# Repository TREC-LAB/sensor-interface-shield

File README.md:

# PCB Sensor Shield V1.4

## V1.4

V1.4 is the lastest sensor shield and as of 11/8/2022 the current shield on PANDORA

## V2.0 and above

These are actually older than 1.4 and were an old labelling system

## See Connor & Nick, I am learning this readme.md stuff :D

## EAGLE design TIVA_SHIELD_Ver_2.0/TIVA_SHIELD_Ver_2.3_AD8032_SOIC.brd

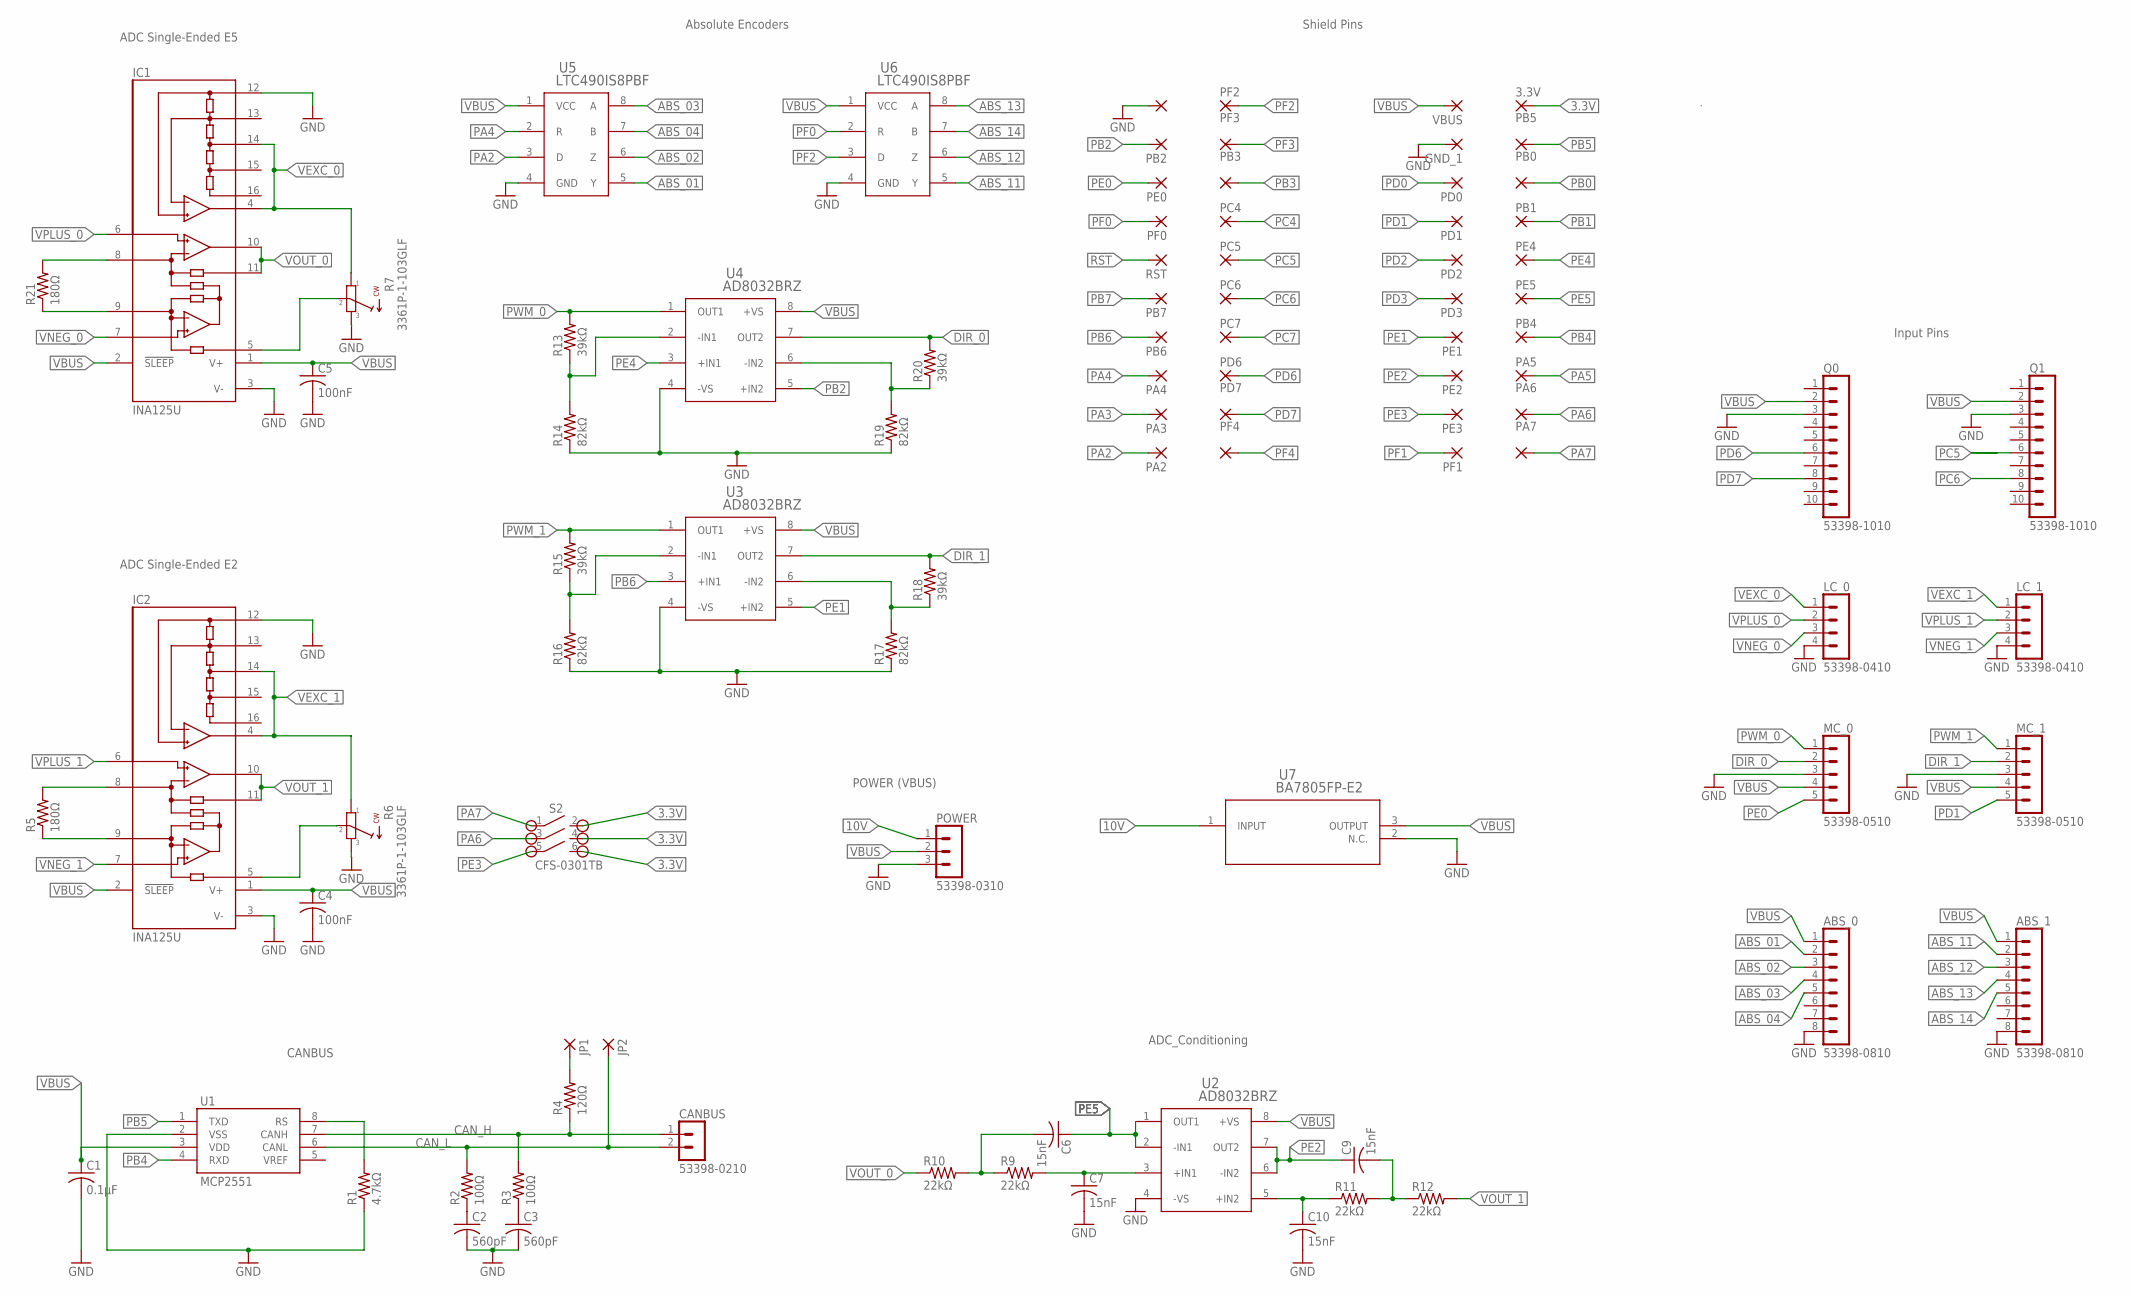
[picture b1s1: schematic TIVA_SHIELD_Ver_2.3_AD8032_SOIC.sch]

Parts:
3.3V: 1,6/0,9
ABS_0, ABS_1: 53398-0810
C1: 0.1µF; C0805
C2, C3: 560pF; C0805
C4, C5: 100nF; C0805
C6, C7, C9, C10: 15nF; C0805
CANBUS: 53398-0210
GND_0, GND_1: 1,6/0,9
IC1, IC2: INA125U; SO16-1
JP1, JP2: 1,6/0,9
LC_0, LC_1: 53398-0410
MC_0, MC_1: 53398-0510
PA2, PA3, PA4, PA5, PA6, PA7: 1,6/0,9
PB0, PB1, PB2, PB3, PB4, PB5, PB6, PB7: 1,6/0,9
PC4, PC5, PC6, PC7: 1,6/0,9
PD0, PD1, PD2, PD3, PD6, PD7: 1,6/0,9
PE0, PE1, PE2, PE3, PE4, PE5: 1,6/0,9
PF0, PF1, PF2, PF3, PF4: 1,6/0,9
POWER: 53398-0310
Q0, Q1: 53398-1010
R1: 4.7kΩ; R0805
R2, R3: 100Ω; R0805
R4: 120Ω; R0805
R5, R21: 180Ω; R0805
R6, R7: 3361P-1-103GLF
R9, R10, R11, R12: 22kΩ; R0805
R13, R15, R18, R20: 39kΩ; R0805
R14, R16, R17, R19: 82kΩ; R0805
RST: 1,6/0,9
S2: CFS-0301TB
U1: MCP2551; SO08
U2, U3, U4: AD8032BRZ; R_8_ADI
U5, U6: LTC490IS8PBF; SO-8_S
U7: BA7805FP-E2; TO252-3_ROM
VBUS: 1,6/0,9

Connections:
3.3V: 3.3V.1, S2.2, S2.4, S2.6
10V: POWER.1, U7.1 (INPUT)
ABS_01: ABS_0.2, U5.5 (Y)
ABS_02: ABS_0.3, U5.6 (Z)
ABS_03: ABS_0.4, U5.8 (A)
ABS_04: ABS_0.5, U5.7 (B)
ABS_11: ABS_1.2, U6.5 (Y)
ABS_12: ABS_1.3, U6.6 (Z)
ABS_13: ABS_1.4, U6.8 (A)
ABS_14: ABS_1.5, U6.7 (B)
CAN_H: CANBUS.1, R3.2, R4.1, U1.7 (CANH)
CAN_L: CANBUS.2, JP2.1, R2.2, U1.6 (CANL)
DIR_0: MC_0.2, R20.2, U4.7 (OUT2)
DIR_1: MC_1.2, R18.2, U3.7 (OUT2)
GND: ABS_0.8, ABS_1.8, C1.2, C2.2, C3.2, C4.2, C5.2, C7.2, C10.2, GND_0.1, GND_1.1, IC1.3 (V-), IC1.12 (REFCOM), IC2.3 (V-), IC2.12 (REFCOM), LC_0.4, LC_1.4, MC_0.3, MC_1.3, POWER.3, Q0.3, Q1.3, R1.1, R6.3, R7.3, R14.1, R16.1, R17.1, R19.1, U1.2 (VSS), U2.4 (-VS), U3.4 (-VS), U4.4 (-VS), U5.4 (GND), U6.4 (GND), U7.2 (N.C.)
unnamed: R1.2, U1.8 (RS)
unnamed: C2.1, R2.1
unnamed: C3.1, R3.1
unnamed: JP1.1, R4.2
unnamed: IC2.9 (RG), R5.1
unnamed: IC2.8 (RG), R5.2
unnamed: IC2.5 (REF), R6.2
unnamed: IC1.9 (RG), R21.1
unnamed: IC1.8 (RG), R21.2
unnamed: IC1.5 (REF), R7.2
unnamed: C10.1, R11.1, U2.5 (+IN2)
unnamed: C9.2, R11.2, R12.1
unnamed: C7.1, R9.2, U2.3 (+IN1)
unnamed: R19.2, R20.1, U4.6 (-IN2)
unnamed: R17.2, R18.1, U3.6 (-IN2)
unnamed: C6.2, R9.1, R10.2
unnamed: R13.1, R14.2, U4.2 (-IN1)
unnamed: R15.1, R16.2, U3.2 (-IN1)
PA2: PA2.1, U5.3 (D)
PA3: PA3.1
PA4: PA4.1, U5.2 (R)
PA5: PA5.1
PA6: PA6.1, S2.3
PA7: PA7.1, S2.1
PB0: PB0.1
PB1: PB1.1
PB2: PB2.1, U4.5 (+IN2)
PB3: PB3.1
PB4: PB4.1, U1.4 (RXD)
PB5: PB5.1, U1.1 (TXD)
PB6: PB6.1, U3.3 (+IN1)
PB7: PB7.1
PC4: PC4.1
PC5: PC5.1, Q1.6
PC6: PC6.1, Q1.8
PC7: PC7.1
PD0: PD0.1
PD1: MC_1.5, PD1.1
PD2: PD2.1
PD3: PD3.1
PD6: PD6.1, Q0.6
PD7: PD7.1, Q0.8
PE0: MC_0.5, PE0.1
PE1: PE1.1, U3.5 (+IN2)
PE2: C9.1, PE2.1, U2.6 (-IN2), U2.7 (OUT2)
PE3: PE3.1, S2.5
PE4: PE4.1, U4.3 (+IN1)
PE5: C6.1, PE5.1, U2.1 (OUT1), U2.2 (-IN1)
PF0: PF0.1, U6.2 (R)
PF1: PF1.1
PF2: PF2.1, U6.3 (D)
PF3: PF3.1
PF4: PF4.1
PWM_0: MC_0.1, R13.2, U4.1 (OUT1)
PWM_1: MC_1.1, R15.2, U3.1 (OUT1)
RST: RST.1
VBUS: ABS_0.1, ABS_1.1, C1.1, C4.1, C5.1, IC1.1 (V+), IC1.2 (!SLEEP), IC2.1 (V+), IC2.2 (!SLEEP), MC_0.4, MC_1.4, POWER.2, Q0.2, Q1.2, U1.3 (VDD), U2.8 (+VS), U3.8 (+VS), U4.8 (+VS), U5.1 (VCC), U6.1 (VCC), U7.3 (OUTPUT), VBUS.1
VEXC_0: IC1.4 (REFOUT), IC1.14 (REF2.5), LC_0.1, R7.1
VEXC_1: IC2.4 (REFOUT), IC2.14 (REF2.5), LC_1.1, R6.1
VNEG_0: IC1.7 (-IN), LC_0.3
VNEG_1: IC2.7 (-IN), LC_1.3
VOUT_0: IC1.10 (OUT), IC1.11 (SENSE), R10.1
VOUT_1: IC2.10 (OUT), IC2.11 (SENSE), R12.2
VPLUS_0: IC1.6 (+IN), LC_0.2
VPLUS_1: IC2.6 (+IN), LC_1.2

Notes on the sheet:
CANBUS
POWER (VBUS)
Shield Pins
ADC Single-Ended E5
ADC Single-Ended E2
ADC_Conditioning
Absolute Encoders
Input Pins

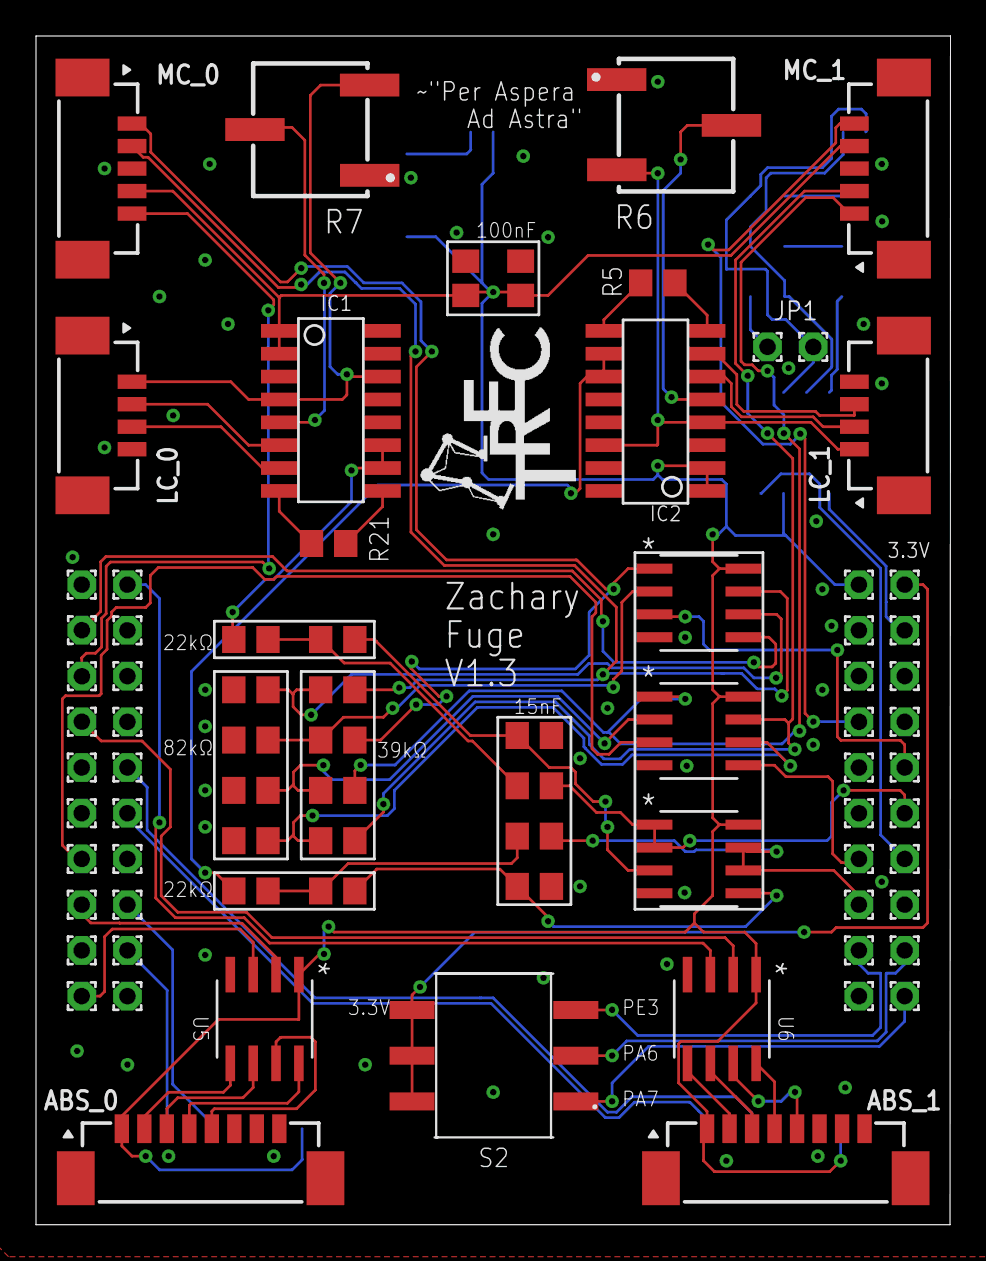
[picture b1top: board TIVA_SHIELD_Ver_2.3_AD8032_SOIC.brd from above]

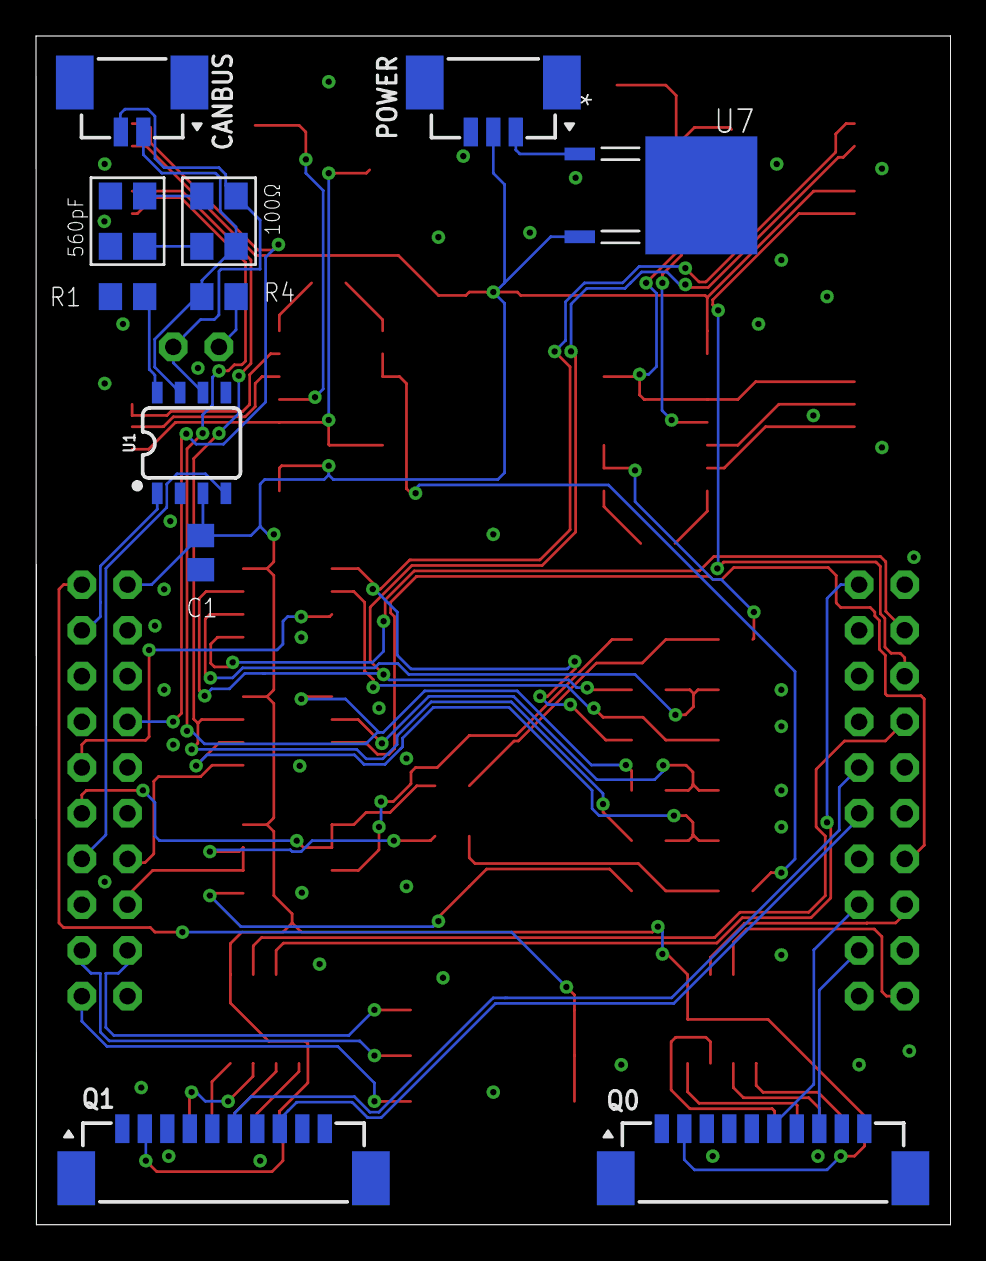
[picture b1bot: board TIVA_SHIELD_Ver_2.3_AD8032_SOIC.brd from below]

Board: 2 copper layers, 50.8 x 66.0 mm, 91 parts (13 on the bottom side), 65 nets.

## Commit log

2022-11-08 PCB V1.4 Project
    Note the current used PCB is V1.4, ignore the V2 as they are actually older
2022-11-09 Zach's Libraries
    Note XT30 Connector needs fixed

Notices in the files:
parts and their libraries:
con-molex-picoblade: Copyright (C) 2010, Bob Starr
SparkFun-IC-Comms: Licensing: Creative Commons ShareAlike 4.0 International - https://creativecommons.org/licenses/by-sa/4.0
COPYRIGHT: Copyright (C) 2021 Ultra Librarian. All rights reserved.
